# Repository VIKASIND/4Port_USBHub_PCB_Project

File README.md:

# 4-Port USB Hub PCB Project
This repository contains the design files for a 4-port USB hub created using KiCad. The project includes the schematic, PCB layout, and 3D renders of the final board. The USB hub design provides an efficient and compact solution to expand USB connectivity for any device.

Project Overview
The 4-port USB hub is designed to expand a single USB connection into four individual ports, making it ideal for connecting multiple devices like flash drives, keyboards, and other peripherals to a computer.

)

Features
4 USB Ports: Supports up to 4 devices with USB 2.0/3.0 compatibility.
Compact Design: Designed for easy integration into various projects.
Powered Hub: Can be modified to support self-powered or bus-powered configurations.
Protection Components: Includes protection diodes and resistors to ensure safe and reliable operation.
3D Render of the PCB

The above image shows a 3D render of the PCB designed in KiCad. It provides a visual representation of the layout, component placement, and overall board design.

Circuit Diagram
The USB hub design is based on standard USB hub controllers with the appropriate supporting components (resistors, capacitors, diodes, and ICs) to ensure functionality and protection. Here's a high-level overview of the circuit:

USB Hub Controller: The main controller IC that manages the distribution of data across the four USB ports.
Decoupling Capacitors: Placed near the power pins of ICs to filter out noise.
Protection Diodes: Used to protect the board from voltage spikes and incorrect power connections.
Crystal Oscillator: Provides the necessary clock signal for the hub controller.
Refer to the schematic in the repository for more detailed information.

KiCad Project Files
The design files for this project are available in the KiCad folder. It includes:

Schematic: The circuit schematic of the USB hub.
PCB Layout: The printed circuit board design.
3D Model: A 3D model of the PCB generated using KiCad's built-in 3D viewer.
To view and edit these files, download KiCad and open the project.

Getting Started
Prerequisites
KiCad: Download and install the latest version of KiCad to view and modify the design files.
3D Viewer: KiCad’s 3D viewer can be used to inspect the 3D models of the PCB.**

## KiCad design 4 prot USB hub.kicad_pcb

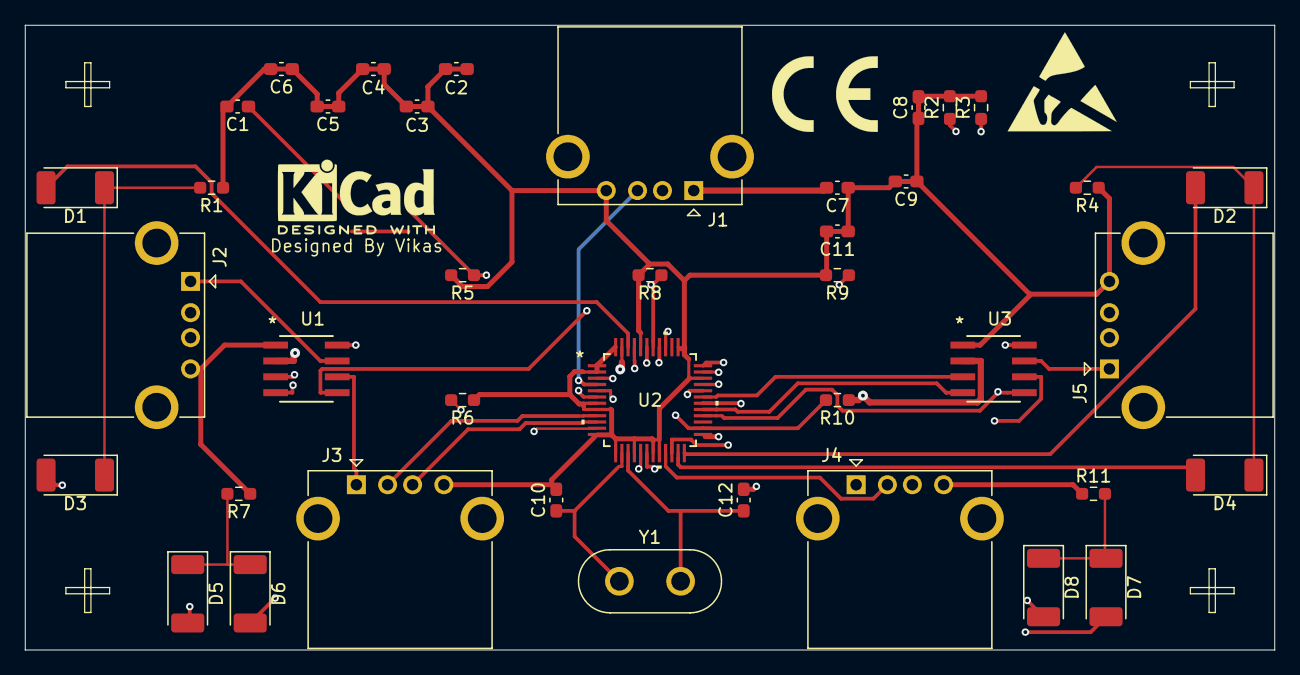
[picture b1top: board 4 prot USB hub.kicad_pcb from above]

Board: 4 copper layers, 100.0 x 50.0 mm, 40 parts (0 on the bottom side), 40 nets.

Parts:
C1: 1uF; C_0603_1608Metric_Pad1.08x0.95mm_HandSolder
C2, C3, C4, C5, C6, C8, C11: 0.1uF; C_0603_1608Metric_Pad1.08x0.95mm_HandSolder
C7, C9: 10uF/10V; C_0603_1608Metric_Pad1.08x0.95mm_HandSolder
C10, C12: 20PF; C_0603_1608Metric_Pad1.08x0.95mm_HandSolder
D1, D2, D3, D4, D5, D6, D7, D8: LED; LED_2010_5025Metric_Pad1.52x2.65mm_HandSolder
J1, J2, J3, J4, J5: USB_A; USB_A_CONNFLY_DS1095-WNR0
R1, R4, R7, R11: 680; R_0603_1608Metric_Pad0.98x0.95mm_HandSolder
R2, R3, R8, R9, R10: 10; R_0603_1608Metric_Pad0.98x0.95mm_HandSolder
R5: 47; R_0603_1608Metric_Pad0.98x0.95mm_HandSolder
R6: 649 T1%; R_0603_1608Metric_Pad0.98x0.95mm_HandSolder
U1, U3: AP2182ASG-13; SO8_DIO
U2: CY7C65642-48AXCT; TQFP48_51-85135_INF
Y1: Crystal; Crystal_HC50_Vertical

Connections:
+3V3: C1.2, C2.1, C2.2, C3.1, C3.2, C4.1, C4.2, C5.1, C5.2, C6.1, C6.2, C7.1, C8.1, C8.2, C9.1, C9.2, C10.2, C11.1, C11.2, C12.2, J1.4 (GND), J2.4 (GND), J3.4 (GND), J4.4 (GND), J5.4 (GND), R1.1, R2.2, R3.2, R4.1, R5.2, R6.1, R7.1, R8.2, R9.2, R11.1, U1.1 (GND), U2.1 (VCC_A), U2.2 (GND), U2.7 (VCC_A), U2.8 (GND), U2.12 (VCC_A), U2.13 (GND), U2.16 (VCC_A), U2.19 (VCC_A), U2.20 (GND), U2.25 (SEL48), U2.34 (VCC_A), U2.37 (SELFPWR), U2.38 (VCC_A), U2.44 (SEL27), U2.48 (VCC_A), U3.1 (GND)
AMBER1: D1.2 (A), U2.46 (AMBER[1]_SPI_CS)
AMBER2: D8.2 (A), U2.36 (AMBER[2]/SPI_MOSI/PWR_PIN_POL)
AMBER3: D5.2 (A), U2.33 (AMBER[3]/SET_PORT_NUM2)
AMBER4: D2.2 (A), U2.24 (AMBER[4]/SET_PORT_NUM1)
GREEN1: D3.2 (A), U2.45 (GREEN[1]_SPI_SK_FIXED_PORT1)
GREEN2: D7.2 (A), U2.35 (GREEN[2]/SPI_MISO/PWR_PIN_POL)
GREEN3: D6.2 (A), U2.32 (GREEN[3]/FIXED_PORT3)
GREEN4: D4.2 (A), U2.23 (GREEN[4]/FIXED_PORT4)
Inout_D+: J1.3 (D+), U2.4 (D+)
unnamed: D1.1 (K), D3.1 (K), R1.2
unnamed: D7.1 (K), D8.1 (K), R11.2
unnamed: D5.1 (K), D6.1 (K), R7.2
unnamed: D2.1 (K), D4.1 (K), R4.2
unnamed: R6.2, U2.11 (RREF)
OVR1: R8.1, U1.5 (FLG2), U2.42 (OVR#[1])
OVR2: R9.1, U1.8 (FLG1), U2.40 (OVR#[2])
OVR3: R3.1, U2.30 (OVR#3), U3.8 (FLG1)
OVR4: R2.1, U2.28 (OVR#[4]), U3.5 (FLG2)
Out_D+1: J2.3 (D+), U2.6 (DD+)
Out_D+2: J3.3 (D+), U2.10 (DD+[2])
Out_D+3: J5.3 (D+), U2.18 (DD+[3])
Out_D+4: J4.3 (D+), U2.22 (DD+[4])
Out_D-1: J2.2 (D-), U2.5 (DD-)
Out_D-2: J3.2 (D-), U2.9 (DD-[2])
Out_D-3: J5.2 (D-), U2.17 (DD-[3])
Out_D-4: J4.2 (D-), U2.21 (DD-[4])
PWR1: U1.4 (EN2), U2.43 (PWR#[1]_I2C_SDA)
PWR2: U1.3 (EN1), U2.41 (PWR#[2])
PWR3: U2.31 (PWR3#), U3.3 (EN1)
PWR4: U2.29 (PWR#[4]), U3.4 (EN2)
RESET: C1.1, R5.1, R10.2, U2.26 (RESET#)
USB_OUT1: J2.1 (VBUS), U1.7 (OUT1)
USB_OUT2: J3.1 (VBUS), U1.6 (OUT2)
USB_OUT3: J5.1 (VBUS), U3.7 (OUT1)
USB_OUT4: J4.1 (VBUS), U3.6 (OUT2)
VBUS: C7.2, J1.1 (VBUS), R10.1, U1.2 (IN), U2.47 (VCC_A), U3.2 (IN)
XIN-PIN14: C10.1, U2.14 (XIN), Y1.1
XOUT-PIN15: C12.1, U2.15 (XOUT), Y1.2
inout_D-: J1.2 (D-), U2.3 (D-)

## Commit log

2024-09-29 Rename Screenshot 2024-09-29 084538.png to CKT.png
